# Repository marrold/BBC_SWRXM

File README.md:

# BBC_SWRXM

Some experiments with Sideways ROM and RAM for the BBC Micro.

**Note:** Currently untested

## License

- This project is licensed under the MIT license

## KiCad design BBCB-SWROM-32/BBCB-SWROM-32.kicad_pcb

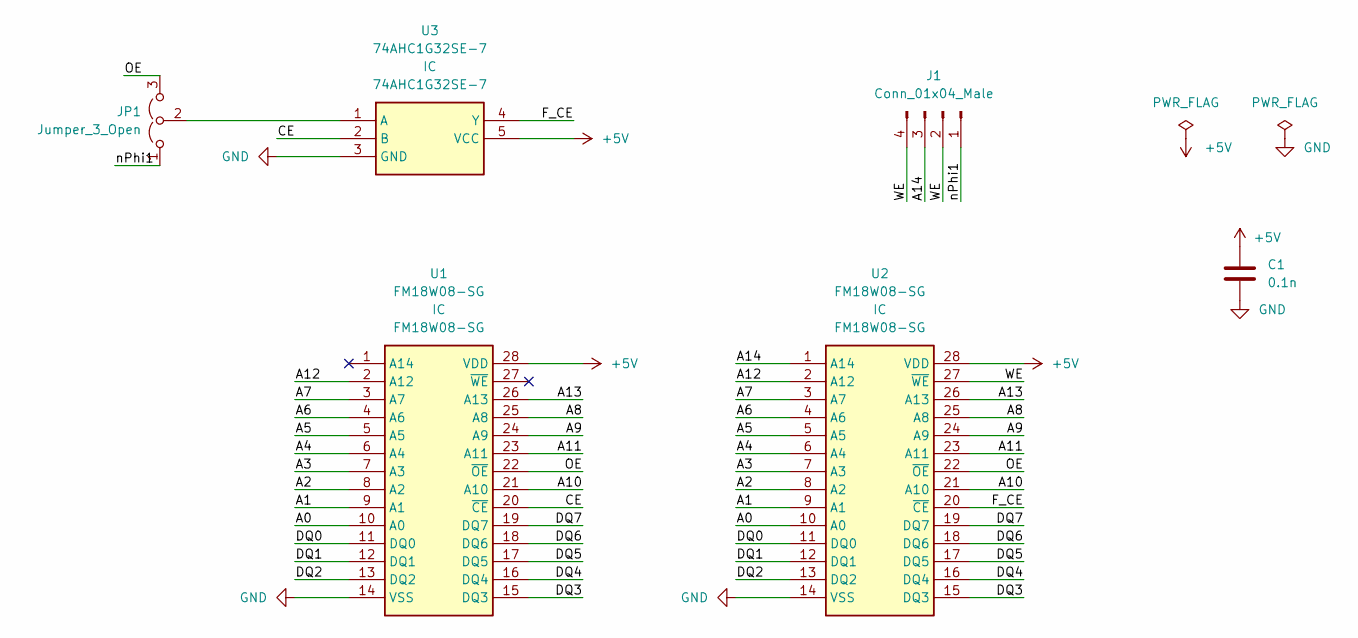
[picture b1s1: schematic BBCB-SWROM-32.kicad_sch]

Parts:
C1: 0.1n; C_0805_2012Metric
J1: Conn_01x04_Male; PinHeader_1x04_P2.54mm_Horizontal
JP1: Jumper_3_Open; SolderJumper-3_P2.0mm_Open_TrianglePad1.0x1.5mm_NumberLabels
U1: FM18W08-SG; DIP-28_W15.24mm; Mouser Part Number 877-FM18W08-SG
U2: FM18W08-SG; FM18W08; Mouser Part Number 877-FM18W08-SG
U3: 74AHC1G32SE-7; SOT65P210X110-5N; Mouser Part Number 621-74AHC1G32SE-7

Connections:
+5V: C1.1, U1.28 (VDD), U2.28 (VDD), U3.5 (VCC)
/A0: U1.10 (A0), U2.10 (A0)
/A1: U1.9 (A1), U2.9 (A1)
/A2: U1.8 (A2), U2.8 (A2)
/A3: U1.7 (A3), U2.7 (A3)
/A4: U1.6 (A4), U2.6 (A4)
/A5: U1.5 (A5), U2.5 (A5)
/A6: U1.4 (A6), U2.4 (A6)
/A7: U1.3 (A7), U2.3 (A7)
/A8: U1.25 (A8), U2.25 (A8)
/A9: U1.24 (A9), U2.24 (A9)
/A10: U1.21 (A10), U2.21 (A10)
/A11: U1.23 (A11), U2.23 (A11)
/A12: U1.2 (A12), U2.2 (A12)
/A13: U1.26 (A13), U2.26 (A13)
/A14: J1.3, U2.1 (A14)
/CE: U1.20 (~CE), U3.2 (B)
/DQ0: U1.11 (DQ0), U2.11 (DQ0)
/DQ1: U1.12 (DQ1), U2.12 (DQ1)
/DQ2: U1.13 (DQ2), U2.13 (DQ2)
/DQ3: U1.15 (DQ3), U2.15 (DQ3)
/DQ4: U1.16 (DQ4), U2.16 (DQ4)
/DQ5: U1.17 (DQ5), U2.17 (DQ5)
/DQ6: U1.18 (DQ6), U2.18 (DQ6)
/DQ7: U1.19 (DQ7), U2.19 (DQ7)
/F_CE: U2.20 (~CE), U3.4 (Y)
/OE: JP1.3 (B), U1.22 (~OE), U2.22 (~OE)
/WE: J1.2, J1.4, U2.27 (~WE)
/nPhi1: J1.1, JP1.1 (A)
GND: C1.2, U1.14 (VSS), U2.14 (VSS), U3.3 (GND)
unnamed: JP1.2 (C), U3.1 (A)

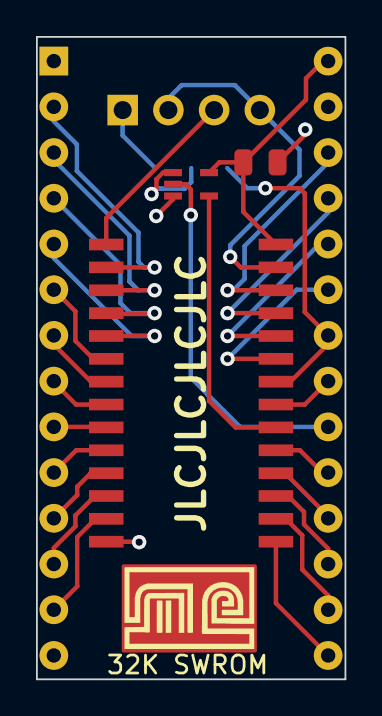
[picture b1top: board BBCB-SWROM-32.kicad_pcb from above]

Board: 2 copper layers, 17.1 x 35.7 mm, 6 parts (1 on the bottom side), 31 nets.

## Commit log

2024-01-03 init
